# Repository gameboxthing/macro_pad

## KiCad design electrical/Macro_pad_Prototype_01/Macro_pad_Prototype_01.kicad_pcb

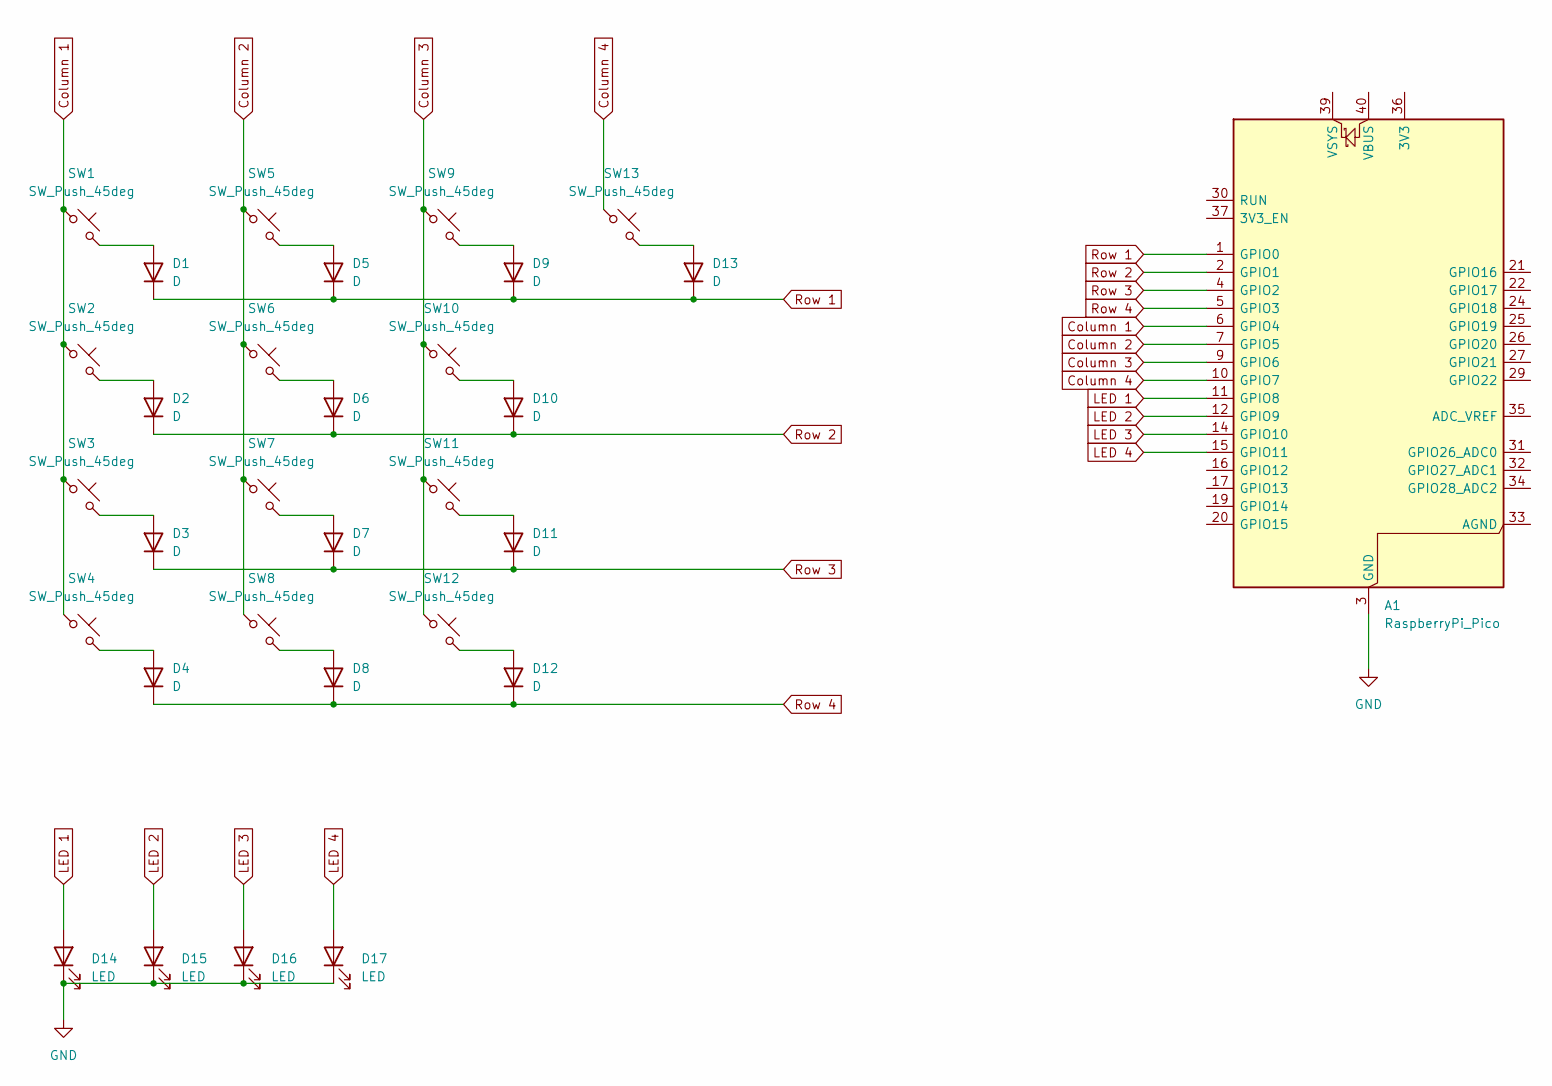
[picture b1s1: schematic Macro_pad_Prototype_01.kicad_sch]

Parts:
A1: RaspberryPi_Pico; RaspberryPi_Pico_Common_Unspecified
D1, D2, D3, D4, D5, D6, D7, D8, D9, D10, D11, D12, D13: D; D_SOD-123
D14, D15, D16, D17: LED; LED_1206_3216Metric_Pad1.42x1.75mm_HandSolder
SW1, SW2, SW3, SW4, SW5, SW6, SW7, SW8, SW9, SW10, SW11, SW12, SW13: SW_Push_45deg; SW_Cherry_MX_PCB_1.00u

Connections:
Column 1: A1.6 (GPIO4), SW1.1, SW2.1, SW3.1, SW4.1
Column 2: A1.7 (GPIO5), SW5.1, SW6.1, SW7.1, SW8.1
Column 3: A1.9 (GPIO6), SW9.1, SW10.1, SW11.1, SW12.1
Column 4: A1.10 (GPIO7), SW13.1
GND: A1.3 (GND), A1.8 (GND), A1.13 (GND), A1.18 (GND), A1.23 (GND), A1.28 (GND), A1.38 (GND), D14.1 (K), D15.1 (K), D16.1 (K), D17.1 (K)
LED 1: A1.11 (GPIO8), D14.2 (A)
LED 2: A1.12 (GPIO9), D15.2 (A)
LED 3: A1.14 (GPIO10), D16.2 (A)
LED 4: A1.15 (GPIO11), D17.2 (A)
unnamed: D1.2 (A), SW1.2
unnamed: D2.2 (A), SW2.2
unnamed: D3.2 (A), SW3.2
unnamed: D4.2 (A), SW4.2
unnamed: D5.2 (A), SW5.2
unnamed: D6.2 (A), SW6.2
unnamed: D7.2 (A), SW7.2
unnamed: D8.2 (A), SW8.2
unnamed: D9.2 (A), SW9.2
unnamed: D10.2 (A), SW10.2
unnamed: D11.2 (A), SW11.2
unnamed: D12.2 (A), SW12.2
unnamed: D13.2 (A), SW13.2
Row 1: A1.1 (GPIO0), D1.1 (K), D5.1 (K), D9.1 (K), D13.1 (K)
Row 2: A1.2 (GPIO1), D2.1 (K), D6.1 (K), D10.1 (K)
Row 3: A1.4 (GPIO2), D3.1 (K), D7.1 (K), D11.1 (K)
Row 4: A1.5 (GPIO3), D4.1 (K), D8.1 (K), D12.1 (K)

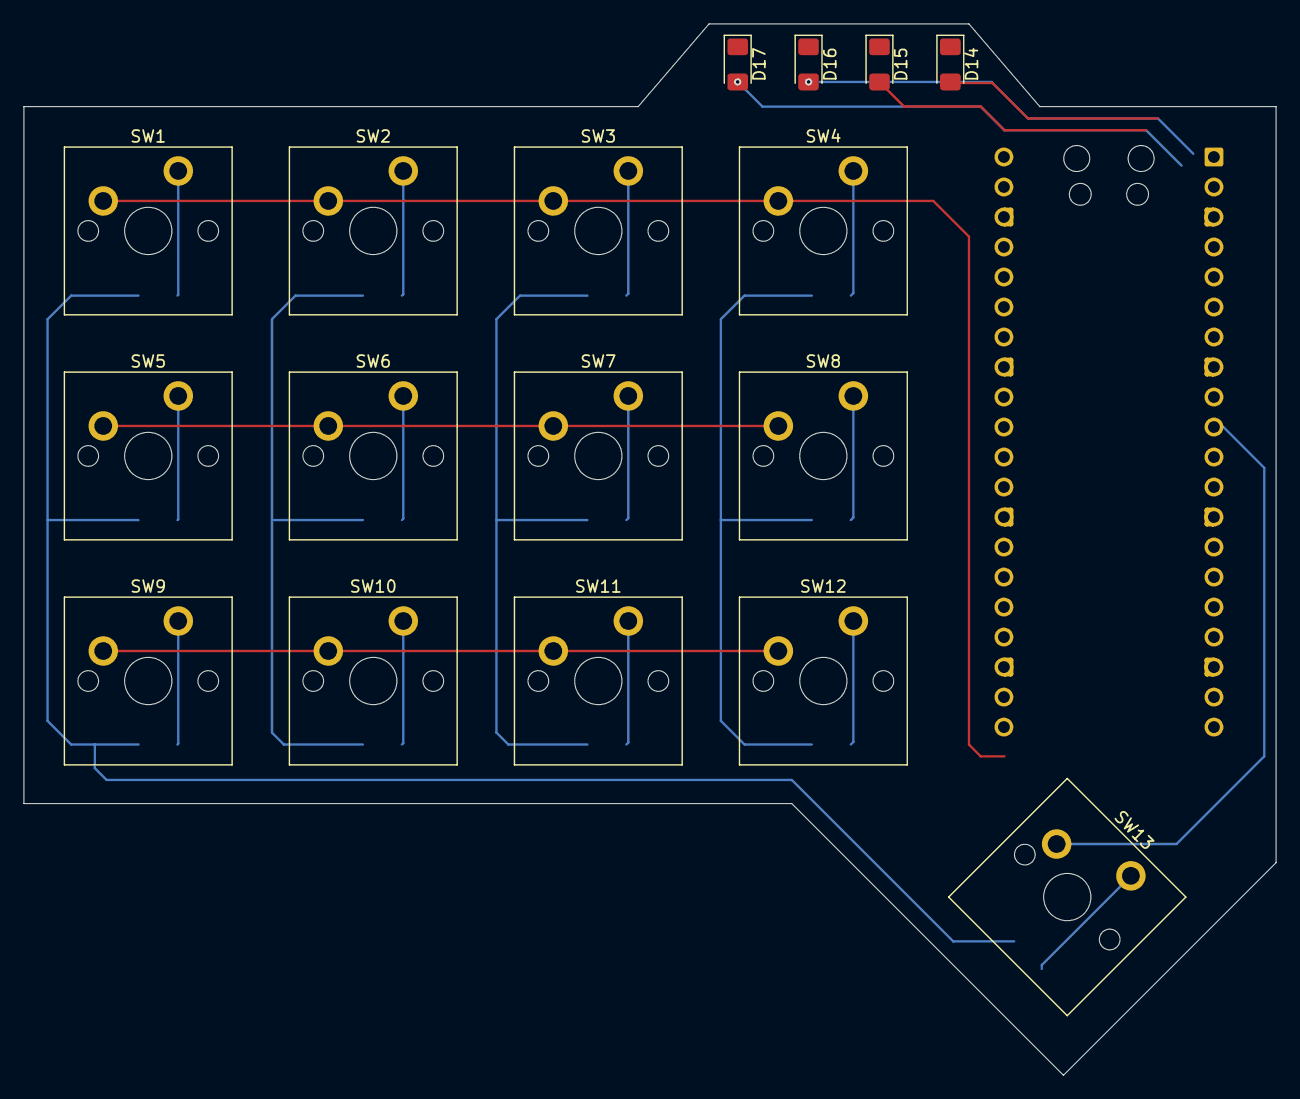
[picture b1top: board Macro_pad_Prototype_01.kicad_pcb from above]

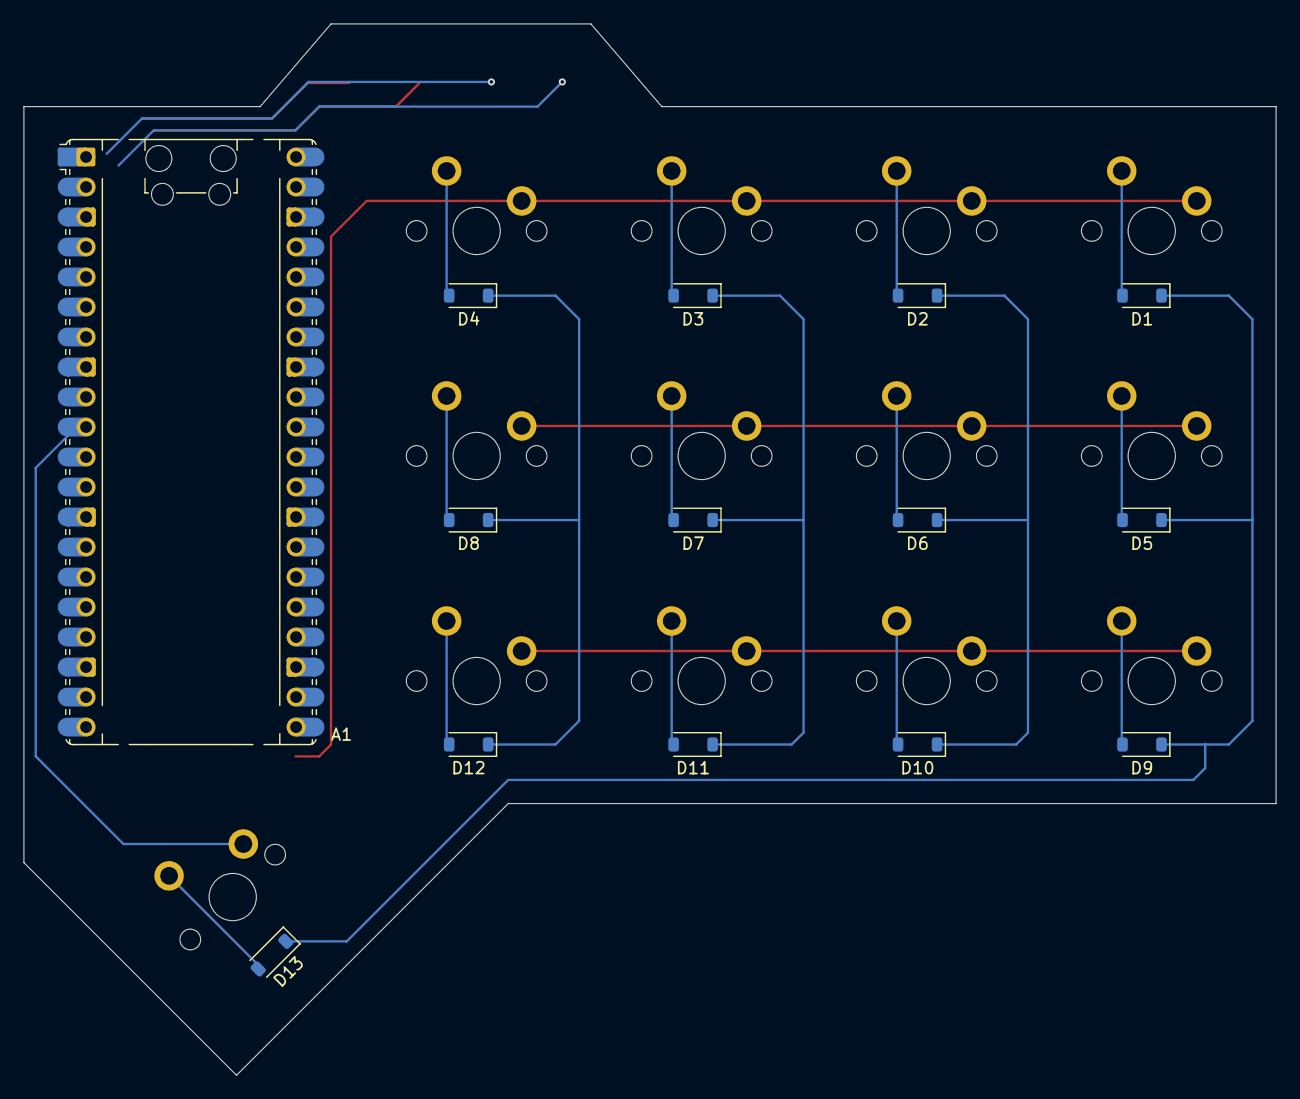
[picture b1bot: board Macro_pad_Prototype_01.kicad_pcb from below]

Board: 2 copper layers, 106.0 x 89.0 mm, 31 parts (14 on the bottom side), 26 nets.

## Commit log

2026-05-09 matrix array schematic done
2026-05-11 base layout complete
